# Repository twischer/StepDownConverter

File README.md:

StepDownConverter
=================

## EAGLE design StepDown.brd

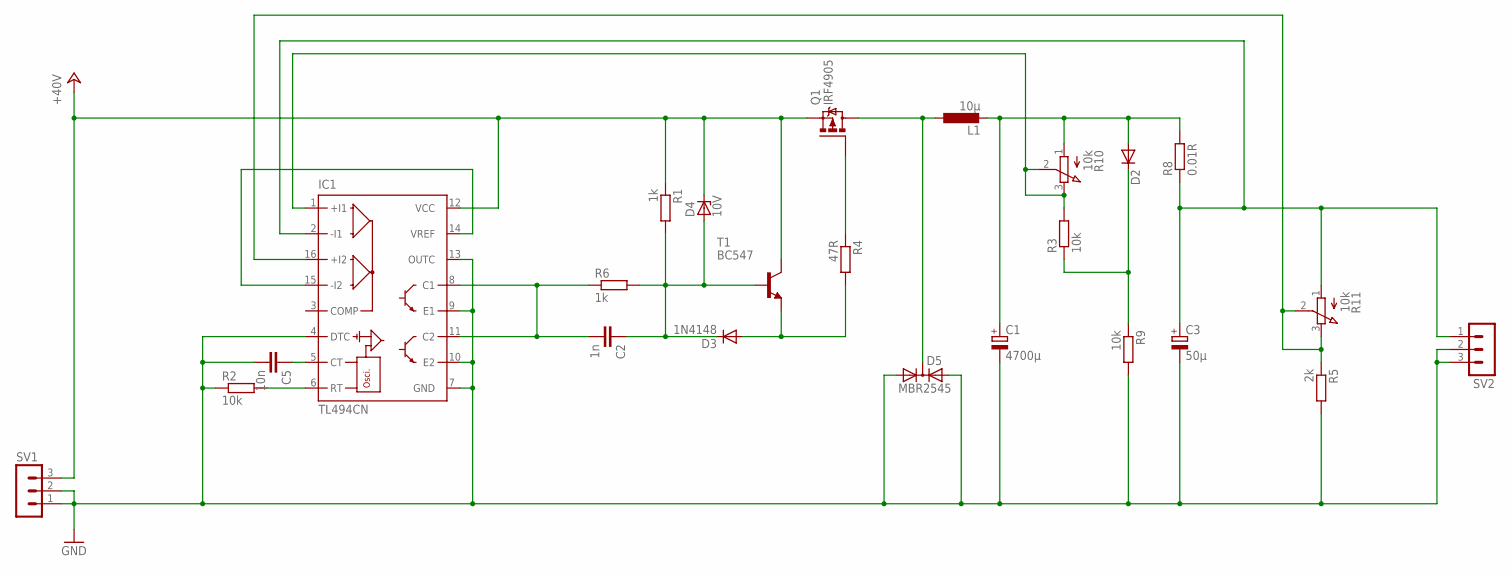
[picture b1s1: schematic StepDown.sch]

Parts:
C1: 4700µ; EB20D
C2: 1n; C025-040X050
C3: 50µ; E2,5-7
C5: 10n; C075-032X103
D2: DIODE-D-10; D-10
D3: 1N4148; D-2.5
D4: 10V; ZDIO-2.5
D5: MBR2545; TO3P
IC1: TL494CN; DIL16
L1: 10µ; TFI0307
Q1: IRF4905; TO220BH
R1, R6: 1k; 0204V
R2, R3, R9: 10k; 0204V
R4: 47R; 0204V
R5: 2k; 0207/12
R8: 0.01R; 0617V
R10, R11: 10k; EVUE
SV1, SV2: MA03-1
T1: BC547; TO92-CBE

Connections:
+24V: D4.C, IC1.12 (VCC), Q1.S, R1.1, SV1.3, T1.C
GND: C1.-, C3.-, C5.2, D5.1 (A1), D5.3 (A2), IC1.4 (DTC), IC1.7 (GND), IC1.9 (E1), IC1.10 (E2), IC1.13 (OUTC), R2.1, R5.2, R9.2, SV1.1, SV1.2, SV2.2, SV2.3
unnamed: C2.2, IC1.8 (C1), IC1.11 (C2), R6.1
unnamed: C5.1, IC1.5 (CT)
unnamed: IC1.14 (VREF), IC1.15 (-I2)
unnamed: C1.+, D2.A, L1.2, R8.2, R10.1 (A)
unnamed: IC1.1 (+I1), R3.2, R10.2 (S), R10.3 (E)
unnamed: IC1.6 (RT), R2.2
unnamed: D3.A, R4.2, T1.E
unnamed: C2.1, D3.C, D4.A, R1.2, R6.2, T1.B
unnamed: D5.2 (C), L1.1, Q1.D
unnamed: C3.+, IC1.2 (-I1), R8.1, R11.1 (A), SV2.1
unnamed: IC1.16 (+I2), R5.1, R11.2 (S), R11.3 (E)
unnamed: D2.C, R3.1, R9.1
unnamed: Q1.G, R4.1

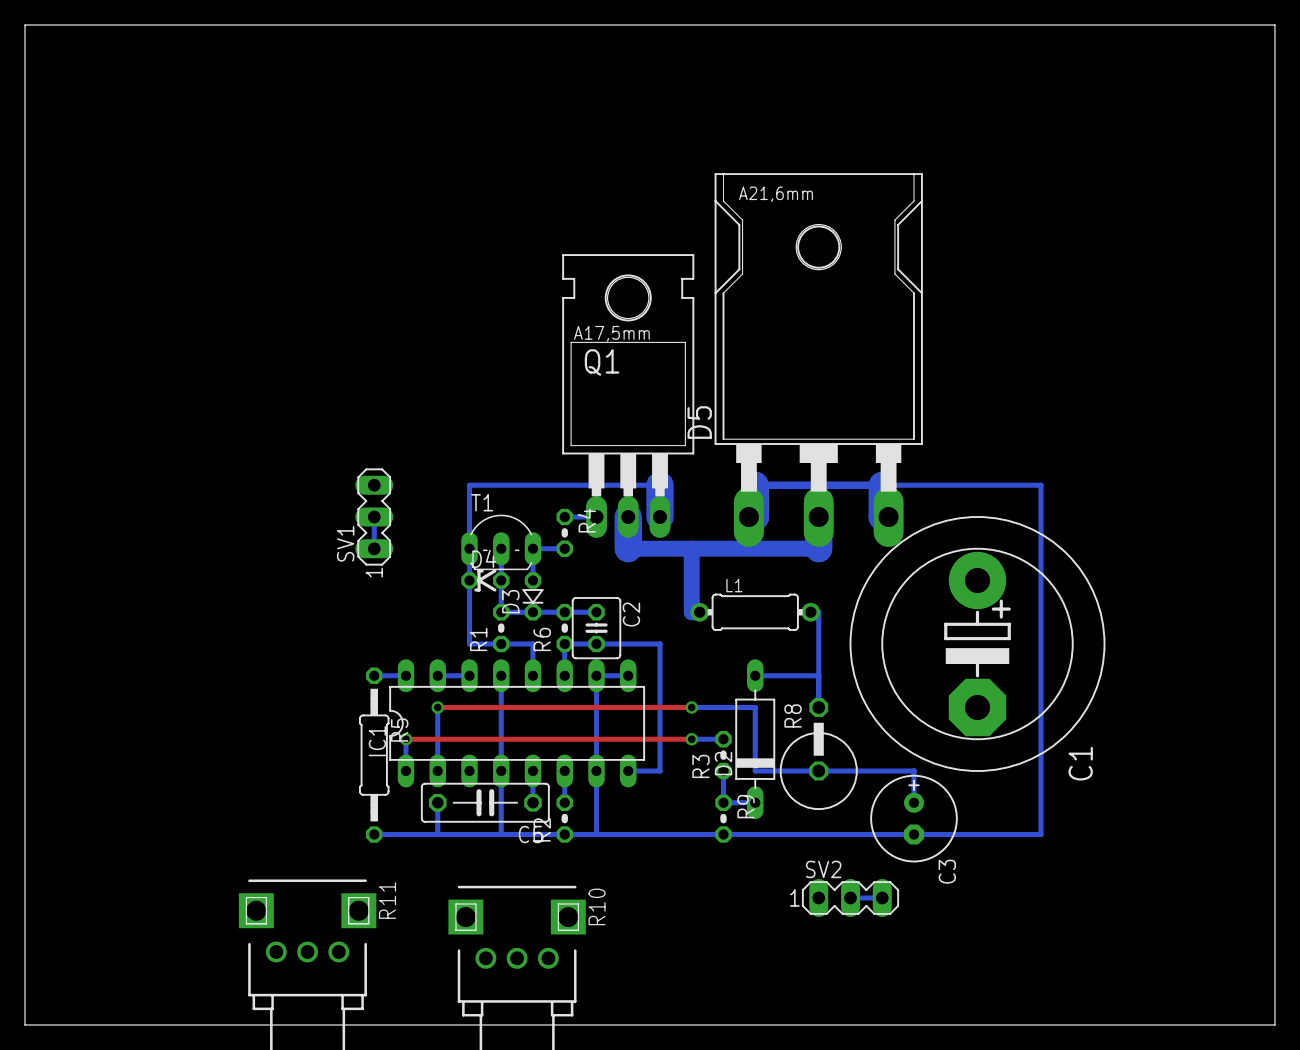
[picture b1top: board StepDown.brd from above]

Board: 2 copper layers, 100.0 x 80.0 mm, 24 parts (0 on the bottom side), 15 nets.

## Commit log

2013-09-07 Converter with TIP32 (not tested)
2013-09-07 Add current sense (not tested)
2013-09-07 Use MOSFET for more than 25A (tested and working)
